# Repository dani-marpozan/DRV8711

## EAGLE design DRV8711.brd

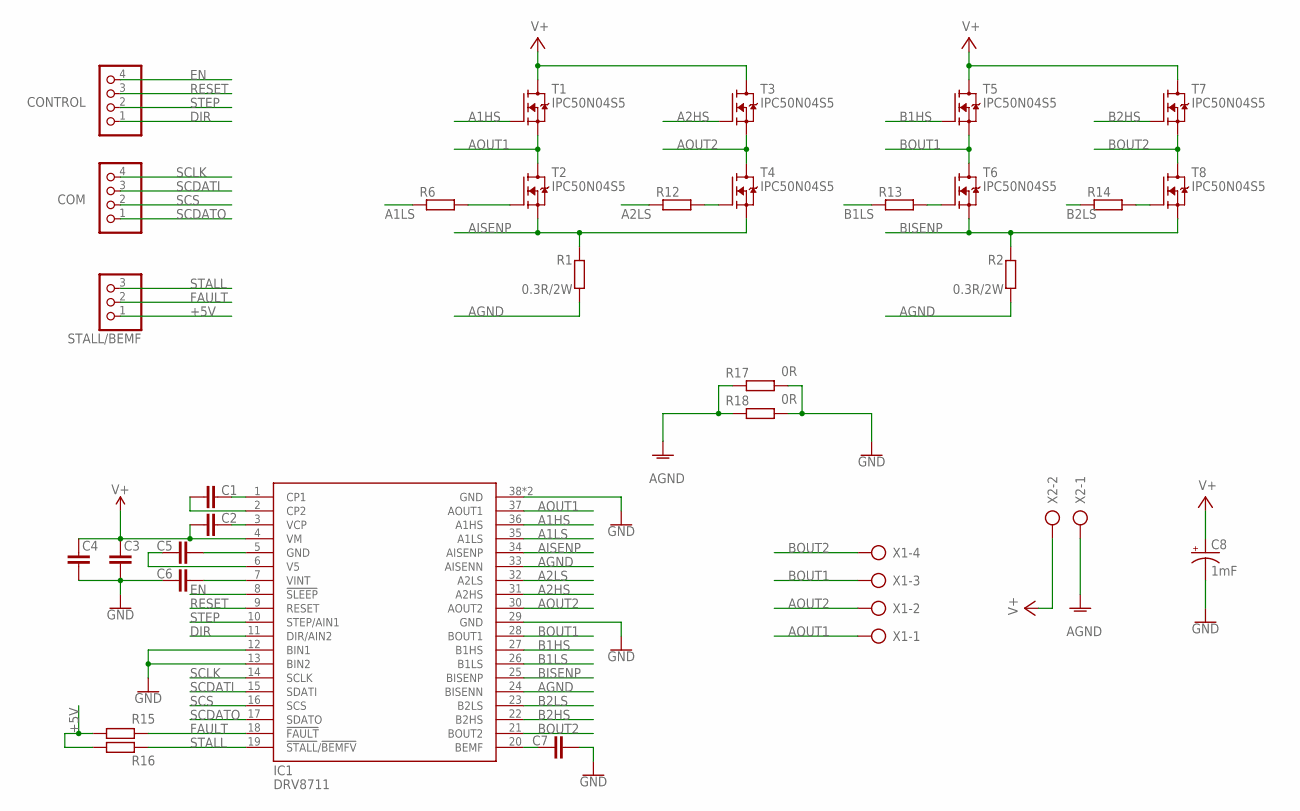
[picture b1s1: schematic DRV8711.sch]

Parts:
C1, C2, C3, C4, C5, C6, C7: C-EUC0805; C0805
C8: 1mF; CPOL-RADIAL-5MM-10MM
COM: PINHD-1X4; 1X04
CONTROL: PINHD-1X4; 1X04
IC1: DRV8711; R-PDSO-G38
R1, R2: 0.3R/2W; R2512
R6, R12, R13, R14, R15, R16: R-EU_R0805; R0805
R17, R18: 0R; R0805
STALL/BEMF: PINHD-1X3; 1X03
T1, T2, T3, T4, T5, T6, T7, T8: IPC50N04S5; PG-TDSON-8-33
X1: AK500/4
X2: AK500/2

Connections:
+5V: R15.2, R16.2, STALL/BEMF.1
A1HS: IC1.36 (A1HS), T1.3 (G)
A1LS: IC1.35 (A1LS), R6.1
A2HS: IC1.31 (A2HS), T3.3 (G)
A2LS: IC1.32 (A2LS), R12.1
AGND: IC1.24 (BISENN), IC1.33 (AISENN), R1.1, R2.1, R17.1, R18.1, X2.1
AISENP: IC1.34 (AISENP), R1.2, T2.2 (S), T4.2 (S)
AOUT1: IC1.37 (AOUT1), T1.2 (S), T2.1 (D), X1.1
AOUT2: IC1.30 (AOUT2), T3.2 (S), T4.1 (D), X1.2
B1HS: IC1.27 (B1HS), T5.3 (G)
B1LS: IC1.26 (B1LS), R13.1
B2HS: IC1.22 (B2HS), T7.3 (G)
B2LS: IC1.23 (B2LS), R14.1
BISENP: IC1.25 (BISENP), R2.2, T6.2 (S), T8.2 (S)
BOUT1: IC1.28 (BOUT1), T5.2 (S), T6.1 (D), X1.3
BOUT2: IC1.21 (BOUT2), T7.2 (S), T8.1 (D), X1.4
DIR: CONTROL.1, IC1.11 (DIR/AIN2)
EN: CONTROL.4, IC1.8 (!SLEEP)
FAULT: IC1.18 (!FAULT), R15.1, STALL/BEMF.2
GND: C3.1, C4.1, C5.1, C6.2, C7.1, C8.-, IC1.5 (GND), IC1.12 (BIN1), IC1.13 (BIN2), IC1.29 (GND), IC1.38 (GND), IC1.PAD (GND), R17.2, R18.2
unnamed: R14.2, T8.3 (G)
unnamed: R6.2, T2.3 (G)
unnamed: R12.2, T4.3 (G)
unnamed: R13.2, T6.3 (G)
unnamed: C1.2, IC1.1 (CP1)
unnamed: C1.1, IC1.2 (CP2)
unnamed: C2.2, IC1.3 (VCP)
unnamed: C7.2, IC1.20 (BEMF)
unnamed: C5.2, IC1.6 (V5)
unnamed: C6.1, IC1.7 (VINT)
RESET: CONTROL.3, IC1.9 (RESET)
SCDATI: COM.3, IC1.15 (SDATI)
SCDATO: COM.1, IC1.17 (SDATO)
SCLK: COM.4, IC1.14 (SCLK)
SCS: COM.2, IC1.16 (SCS)
STALL: IC1.19 (!STALL!/!BEMFV!), R16.1, STALL/BEMF.3
STEP: CONTROL.2, IC1.10 (STEP/AIN1)
V+: C2.1, C3.2, C4.2, C8.+, IC1.4 (VM), T1.1 (D), T3.1 (D), T5.1 (D), T7.1 (D), X2.2

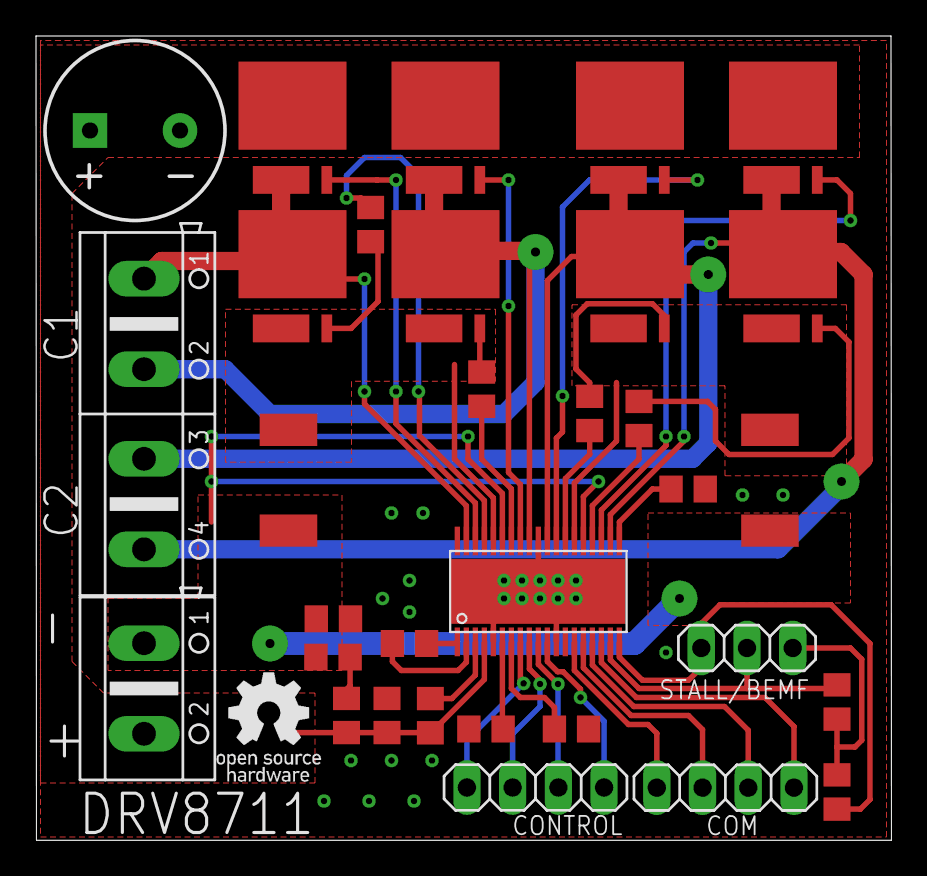
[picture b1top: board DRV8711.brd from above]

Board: 2 copper layers, 47.5 x 44.7 mm, 32 parts (0 on the bottom side), 38 nets.

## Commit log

2019-08-01 Add files via upload
    without 5 parallel resistors

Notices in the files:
parts and their libraries:
SparkFun-Capacitors: Licensing: Creative Commons ShareAlike 4.0 International - https://creativecommons.org/licenses/by-sa/4.0
